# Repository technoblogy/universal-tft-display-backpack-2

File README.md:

# Universal TFT Display Backpack 2
Eagle files for a microcontroller board, based on an ATtiny814, that can accommodate a range of different Adafruit and AliExpress colour TFT displays.

See <http://www.technoblogy.com/show?5O3E>.

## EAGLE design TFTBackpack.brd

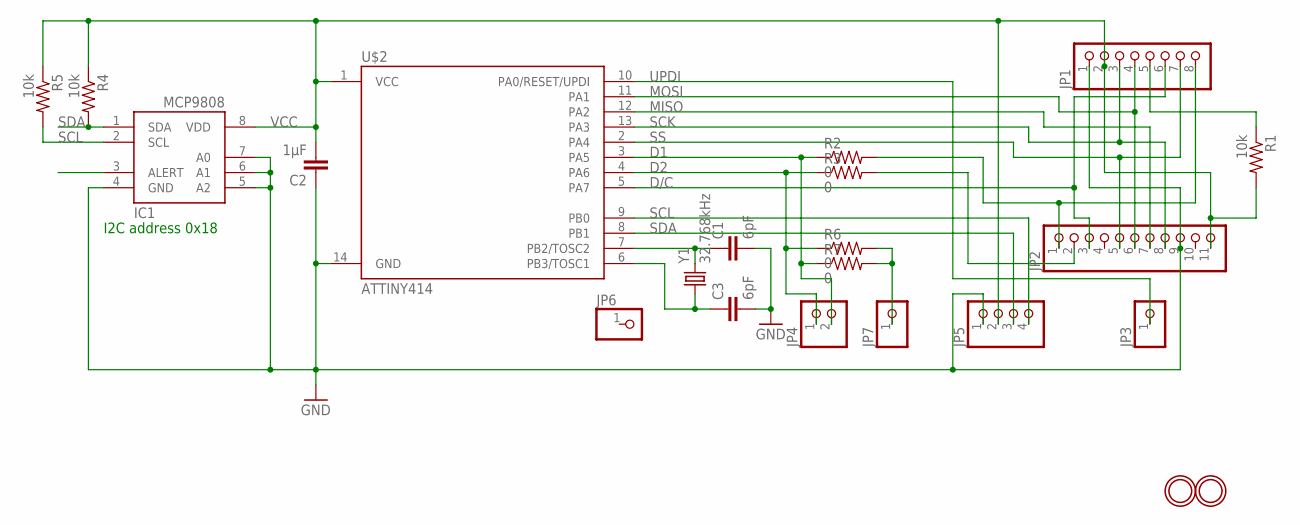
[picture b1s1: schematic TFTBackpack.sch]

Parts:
C1, C3: 6pF; 0805
C2: 1µF; 0805
IC1: MCP9808-E/MS; MSOP8_0.65MM
JP1: HEADER-1X8ROUND; 1X08_ROUND
JP2: HEADER-1X11; 1X11_ROUND
JP3, JP6, JP7: HEADER-1X1ROUND; 1X01_ROUND
JP4: HEADER-1X2ROUND; 1X02_ROUND
JP5: HEADER-1X4ROUND; 1X04_ROUND
R1, R4, R5: 10k; 0805
R2, R3, R6, R7: 0; 0805
U$1, U$9: MOUNTINGHOLE2.5; MOUNTINGHOLE_2.5_PLATED
U$2: ATTINY414; SO14
Y1: 32.768kHz; CRYSTAL-SMD-3.2X1.5MM

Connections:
ALERT: IC1.3 (ALERT)
BL: JP1.8, JP2.1, R2.2
D1: JP4.2, R2.1, R7.1, U$2.3 (PA5)
D2: JP4.1, R3.1, R6.1, U$2.4 (PA6)
D/C: JP1.6, JP2.3, U$2.5 (PA7)
GND: C1.2, C2.1, C3.2, IC1.4 (GND), IC1.5 (A2), IC1.6 (A1), IC1.7 (A0), JP1.1, JP2.9, JP5.1, U$2.14 (GND)
MISO: JP2.7, U$2.12 (PA2)
MOSI: JP1.4, JP2.6, U$2.11 (PA1)
unnamed: JP7.1, R6.2, R7.2
unnamed: C1.1, U$2.7 (PB2/TOSC2), Y1.P$2 (2)
unnamed: C3.1, U$2.6 (PB3/TOSC1), Y1.P$1 (1)
unnamed: JP1.5, R1.1
unnamed: JP2.2, R3.2
SCK: JP1.3, JP2.8, U$2.13 (PA3)
SCL: IC1.2 (SCL), JP5.4, R5.2, U$2.9 (PB0)
SDA: IC1.1 (SDA), JP5.3, R4.2, U$2.8 (PB1)
SS: JP1.7, JP2.5, U$2.2 (PA4)
UPDI: JP3.1, U$2.10 (PA0/RESET/UPDI)
VCC: C2.2, IC1.8 (VDD), JP1.2, JP2.11, JP5.2, R1.2, R4.1, R5.1, U$2.1 (VCC)

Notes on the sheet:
I2C address 0x18

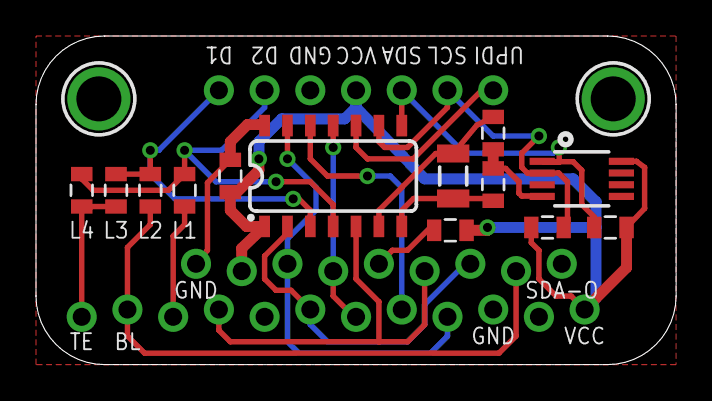
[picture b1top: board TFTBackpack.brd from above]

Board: 2 copper layers, 35.6 x 18.3 mm, 22 parts (0 on the bottom side), 18 nets.

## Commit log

2026-05-02 Version 1 - 2nd May 2026

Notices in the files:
parts and their libraries:
microbuilder: This work is placed in the public domain, and may be freely used for commercial and non-commercial work with the following conditions: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
SparkFun-Capacitors: Licensing: CC v3.0 Share-Alike You are welcome to use this library for commercial purposes.
